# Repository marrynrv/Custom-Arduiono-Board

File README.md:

# Custom ATmega328PB Development Board 

A custom-designed development board built from scratch in **KiCad EDA**, based on the ATmega328PB microcontroller architecture and the classic Arduino Uno reference design. 

This project was created as a practical hands-on hardware engineering task to master schematic capture, SMD component placement, USB-to-UART interface integration, power regulation, and manufacturing output preparation.

---

## 3D Render & Hardware Preview

---

## Hardware Specifications & Key Features

* **Primary Microcontroller:** ATmega328PB-AU (TQFP-32 package)
* **USB-to-Serial Converter:** ATmega16U2-A with 16MHz Crystal Oscillator
* **Power Management:** 
  * NCP1117-5.0 LDO regulator for 5V main rail
  * LP2985-3.3 regulator for 3.3V power output
  * DC Barrel Jack & USB Micro (USB_B_Micro) input protection
* **ESD & Circuit Protection:** ESD protection array (CG00603MLC-05E) and resettable PTC fuse (MF-MSMF050-2)
* **Operational Amplifiers:** LMV358 for power source switching / indicator circuit
* **Programming Interfaces:** AVR-ISP-6 headers for direct flashing via ICSP
* **Design Tools:** KiCad EDA (Schematics, PCB Layout, Gerber generation, BOM export)

---

## Repository Content

* `arduino-board-pcb.kicad_sch` — Schematic source file
* `arduino-board-pcb.kicad_pcb` — PCB layout source file
* `arduino-board-pcb.kicad_pro` — KiCad main project file
* `arduino-board-pcb.csv` — Full Bill of Materials (BOM) with precise component specifications
* `pcb-arduino-gbr.rar` — Production-ready Gerber files
* `/images/board_3d.png` — 3D visualization render

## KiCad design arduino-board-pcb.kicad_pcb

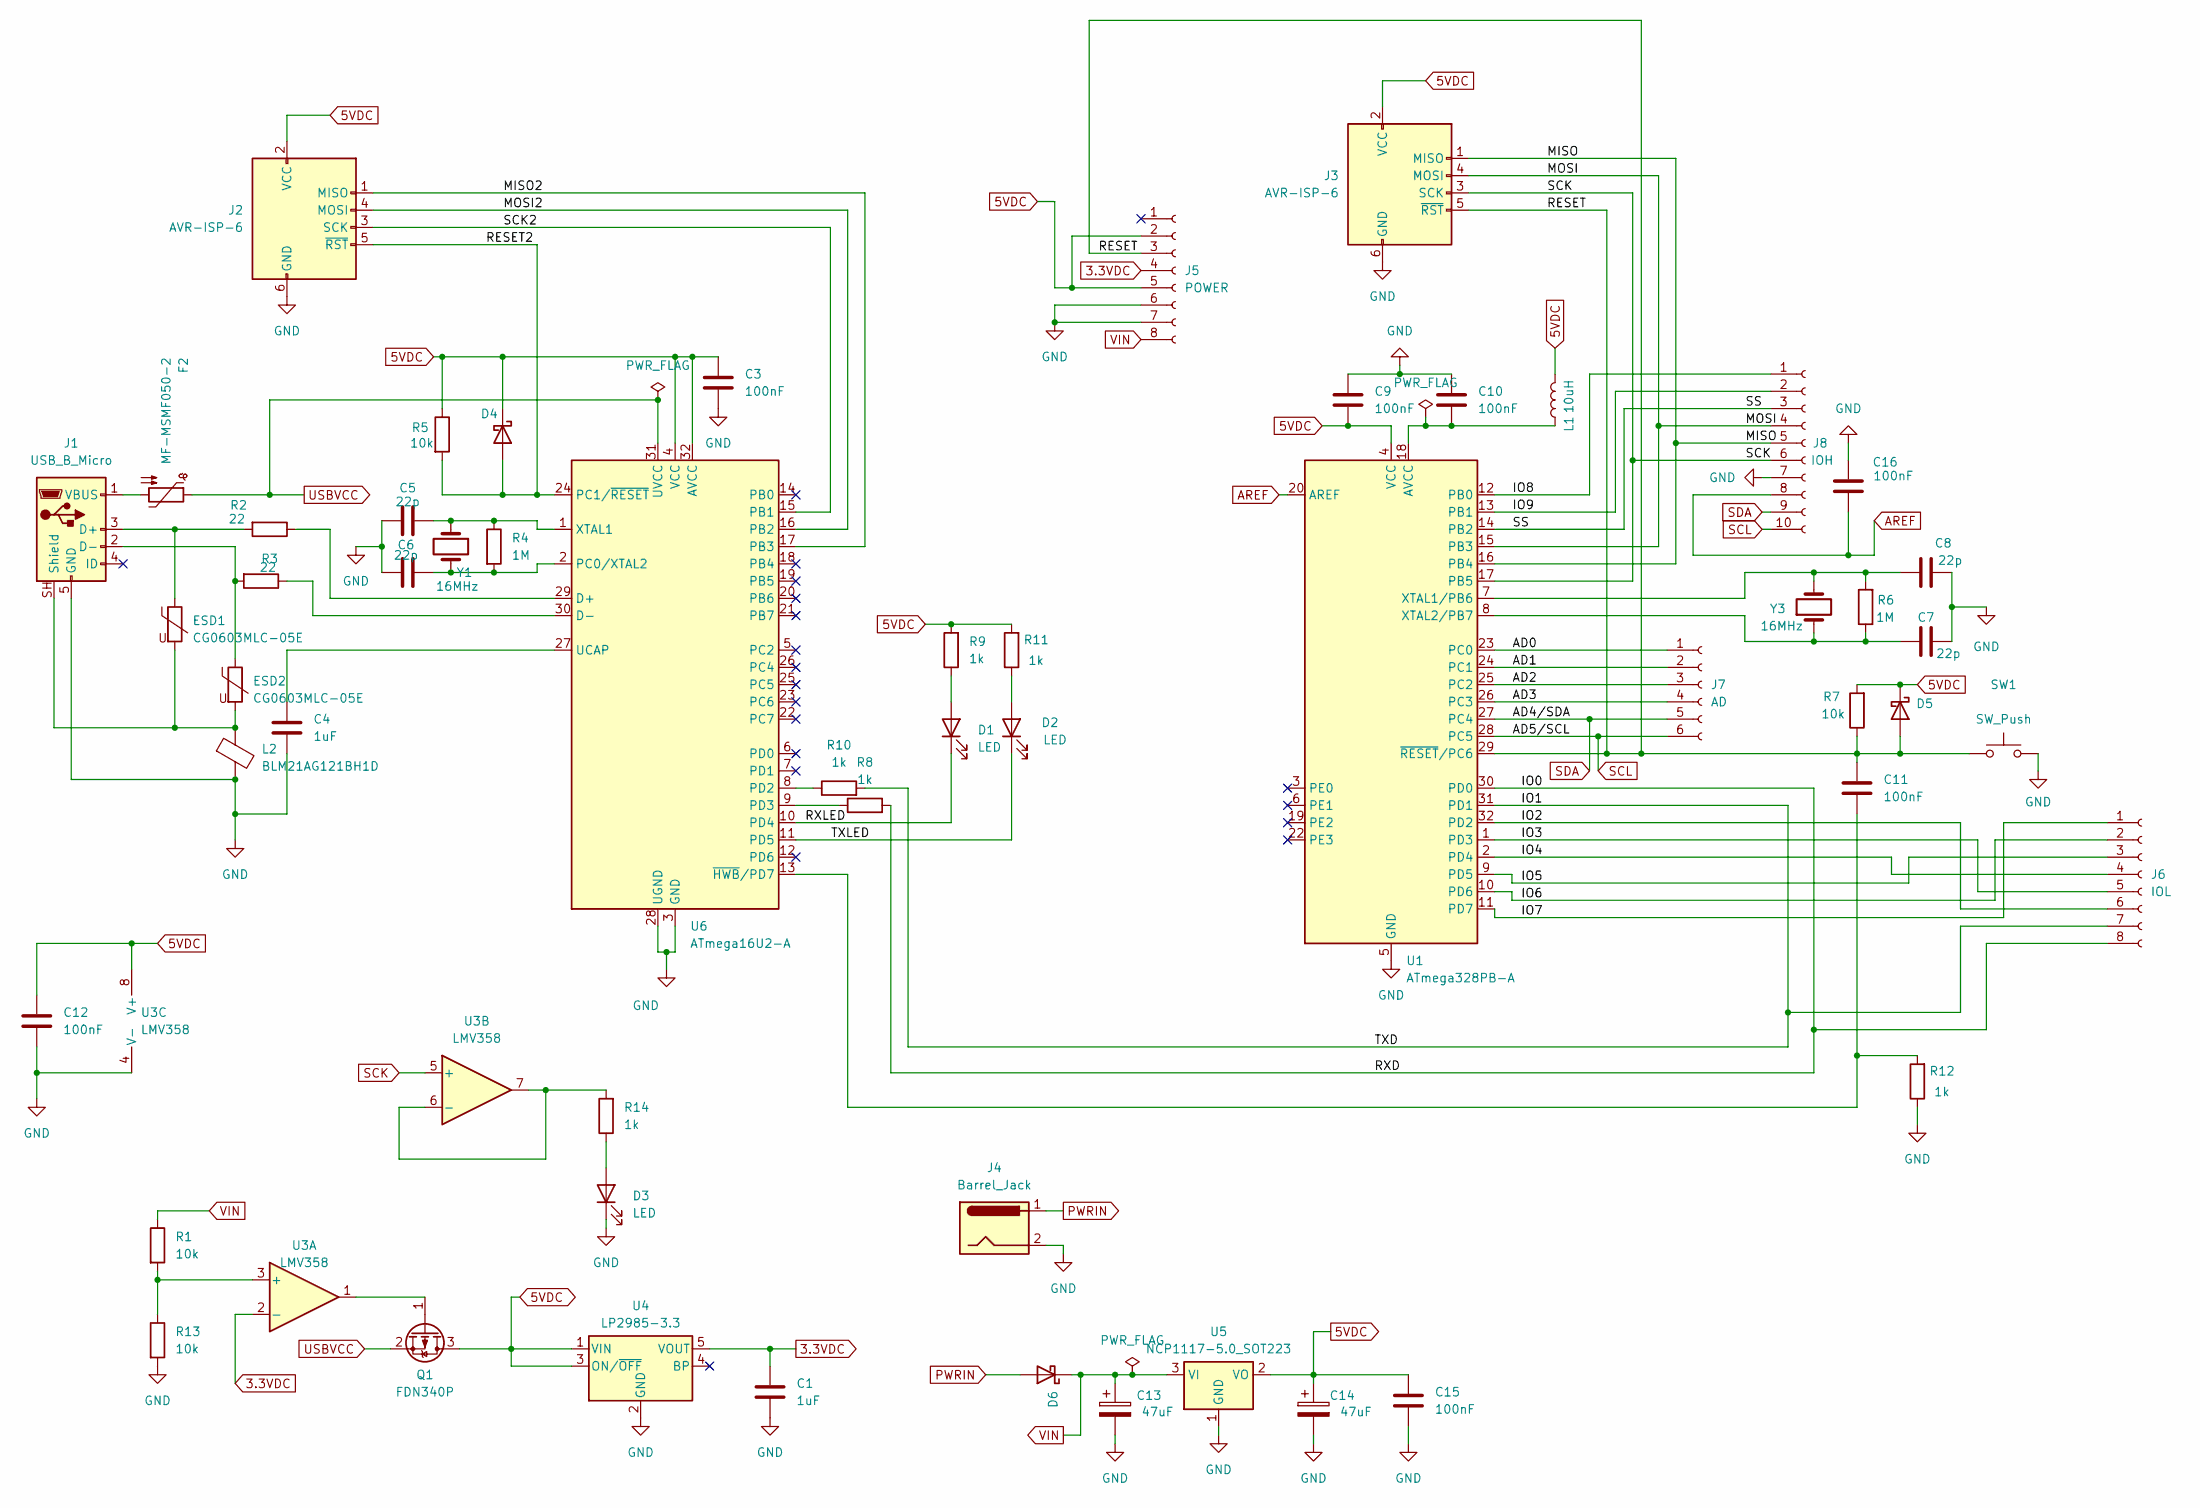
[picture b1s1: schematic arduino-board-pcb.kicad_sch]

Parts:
C1, C4: 1uF; C_0603_1608Metric
C3, C9, C10, C11, C12, C15, C16: 100nF; C_0603_1608Metric
C5, C6, C7, C8: 22p; C_0603_1608Metric
C13, C14: 47uF; CP_Elec_6.3x5.8
D1, D2, D3: LED; LED_0603_1608Metric
D4, D5, D6: CDBA340-HF; D_SMA
ESD1, ESD2: CG0603MLC-05E; R_0603_1608Metric
F2: MF-MSMF050-2; Fuse_1812_4532Metric
J1: USB_B_Micro; USB_Micro-B_Amphenol_10118193-0001LF_Horizontal
J2, J3: AVR-ISP-6; PinHeader_2x03_P2.54mm_Vertical_SMD
J4: Barrel_Jack; BarrelJack_SwitchcraftConxall_RAPC10U_Horizontal
J5: POWER; PinSocket_1x08_P2.54mm_Vertical
J6: IOL; PinSocket_1x08_P2.54mm_Vertical
J7: AD; PinSocket_1x06_P2.54mm_Vertical
J8: IOH; PinSocket_1x10_P2.54mm_Vertical
L1: 10uH; L_0603_1608Metric
L2: BLM21AG121BH1D; L_0805_2012Metric
Q1: FDN340P; SOT-23
R1, R5, R7, R13: 10k; R_0603_1608Metric
R2, R3: 22; R_0603_1608Metric
R4, R6: 1M; R_0603_1608Metric
R8, R9, R10, R11, R12, R14: 1k; R_0603_1608Metric
SW1: SW_Push; SW_Tactile_SPST_NO_Straight_CK_PTS636Sx25SMTRLFS
U1: ATmega328PB-A; TQFP-32_7x7mm_P0.8mm
U3: LMV358; MSOP-8_3x3mm_P0.65mm
U4: LP2985-3.3; SOT-23-5
U5: NCP1117-5.0_SOT223; SOT-223-3_TabPin2
U6: ATmega16U2-A; TQFP-32_7x7mm_P0.8mm
Y1, Y3: 16MHz; Crystal_SMD_Abracon_ABM3-2Pin_5.0x3.2mm

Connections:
3.3VDC: C1.1, J5.4, U3.2 (-), U4.5 (VOUT)
5VDC: C3.1, C9.2, C12.1, C14.1, C15.1, D4.1 (K), D5.1 (K), J2.2 (VCC), J3.2 (VCC), J5.2, J5.5, L1.2, Q1.3 (D), R5.1, R7.2, R9.2, R11.2, U1.4 (VCC), U3.8 (V+), U4.1 (VIN), U4.3 (ON/~OFF), U5.2 (VO), U6.4 (VCC), U6.32 (AVCC)
/AD0: J7.1, U1.23 (PC0)
/AD1: J7.2, U1.24 (PC1)
/AD2: J7.3, U1.25 (PC2)
/AD3: J7.4, U1.26 (PC3)
/IO0: J6.8, R8.2, U1.30 (PD0)
/IO1: J6.7, R10.2, U1.31 (PD1)
/IO2: J6.6, U1.32 (PD2)
/IO3: J6.5, U1.1 (PD3)
/IO4: J6.4, U1.2 (PD4)
/IO5: J6.3, U1.9 (PD5)
/IO6: J6.2, U1.10 (PD6)
/IO7: J6.1, U1.11 (PD7)
/IO8: J8.1, U1.12 (PB0)
/IO9: J8.2, U1.13 (PB1)
/MISO: J3.1 (MISO), J8.5, U1.16 (PB4)
/MISO2: J2.1 (MISO), U6.17 (PB3)
/MOSI: J3.4 (MOSI), J8.4, U1.15 (PB3)
/MOSI2: J2.4 (MOSI), U6.16 (PB2)
/RESET: C11.1, D5.2 (A), J3.5 (~RST), J5.3, R7.1, SW1.1, U1.29 (~RESET/PC6)
/RESET2: D4.2 (A), J2.5 (~RST), R5.2, U6.24 (PC1/~RESET)
/RXLED: D1.1 (K), U6.10 (PD4)
/SCK2: J2.3 (SCK), U6.15 (PB1)
/SS: J8.3, U1.14 (PB2)
/TXLED: D2.1 (K), U6.11 (PD5)
AREF: C16.1, J8.8, U1.20 (AREF)
GND: C1.2, C3.2, C4.2, C5.2, C6.2, C7.2, C8.2, C9.1, C10.1, C12.2, C13.2, C14.2, C15.2, C16.2, D3.1 (K), J1.5 (GND), J2.6 (GND), J3.6 (GND), J4.2, J5.6, J5.7, J8.7, L2.2, R12.1, R13.2, SW1.2, U1.5 (GND), U1.21 (GND), U3.4 (V-), U4.2 (GND), U5.1 (GND), U6.3 (GND), U6.28 (UGND)
unnamed: D1.2 (A), R9.1
unnamed: D2.2 (A), R11.1
unnamed: D3.2 (A), R14.1
unnamed: ESD1.1, J1.3 (D+), R2.2
unnamed: ESD2.1, J1.2 (D-), R3.2
unnamed: ESD1.2, ESD2.2, J1.SH (Shield), L2.1
unnamed: F2.2, J1.1 (VBUS)
unnamed: Q1.1 (G), U3.1
unnamed: C10.2, L1.1, U1.18 (AVCC)
unnamed: C8.1, R6.2, U1.7 (XTAL1/PB6), Y3.2
unnamed: C7.1, R6.1, U1.8 (XTAL2/PB7), Y3.1
unnamed: R1.2, R13.1, U3.3 (+)
unnamed: R14.2, U3.6 (-), U3.7
unnamed: R2.1, U6.29 (D+)
unnamed: R3.1, U6.30 (D-)
unnamed: C6.1, R4.2, U6.2 (PC0/XTAL2), Y1.2
unnamed: R10.1, U6.8 (PD2)
unnamed: R8.1, U6.9 (PD3)
unnamed: C4.1, U6.27 (UCAP)
unnamed: C5.1, R4.1, U6.1 (XTAL1), Y1.1
unnamed: C11.2, R12.2, U6.13 (~HWB/PD7)
PWRIN: D6.2 (A), J4.1
SCK: J3.3 (SCK), J8.6, U1.17 (PB5), U3.5 (+)
SCL: J7.6, J8.10, U1.28 (PC5)
SDA: J7.5, J8.9, U1.27 (PC4)
USBVCC: F2.1, Q1.2 (S), U6.31 (UVCC)
VIN: C13.1, D6.1 (K), J5.8, R1.1, U5.3 (VI)

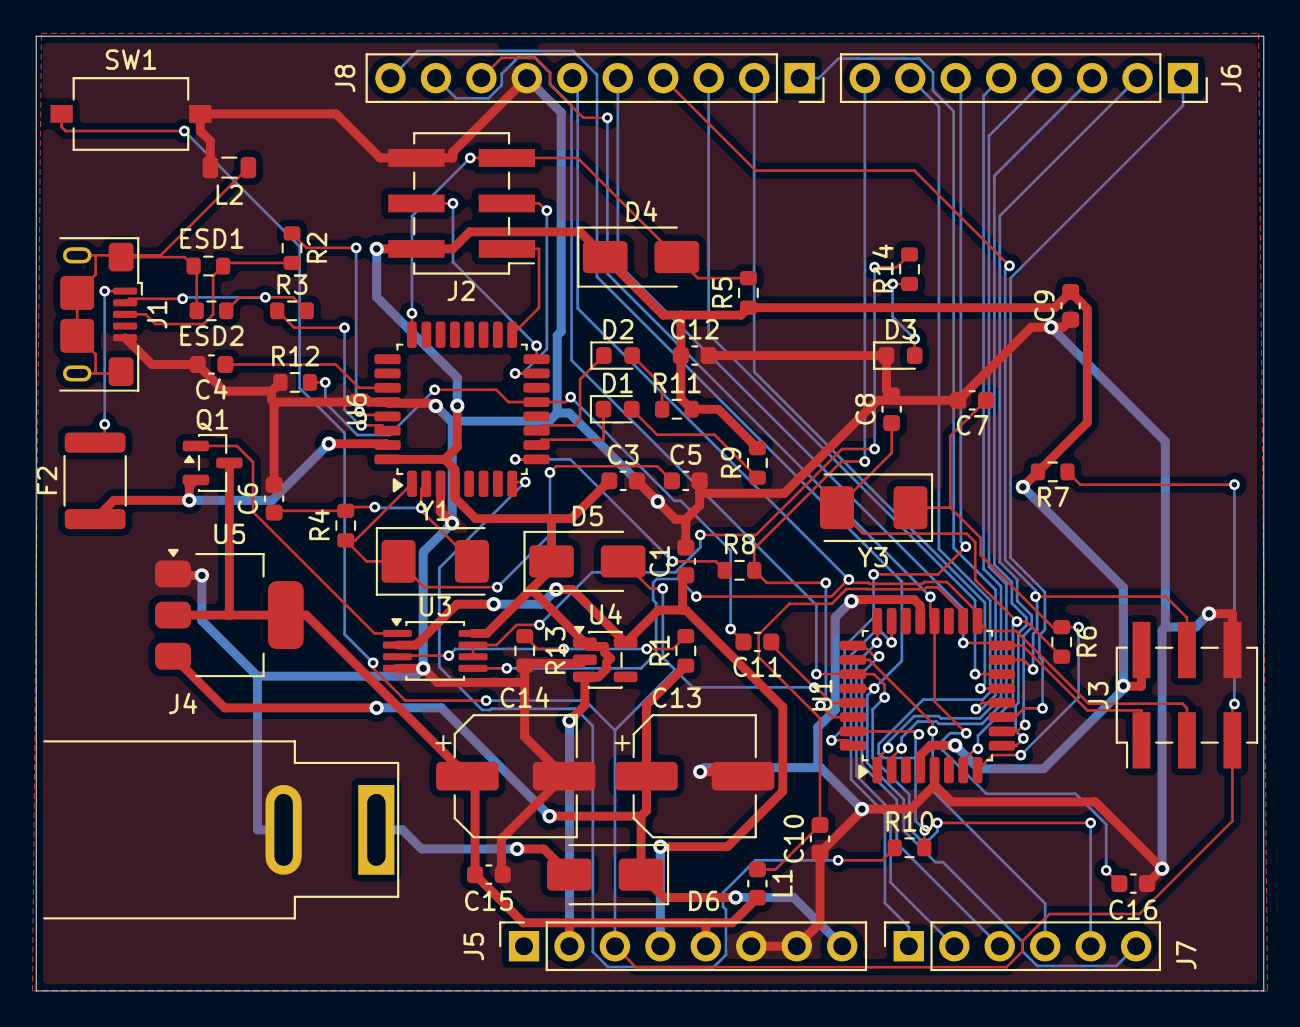
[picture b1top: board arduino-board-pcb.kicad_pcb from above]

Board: 2 copper layers, 68.6 x 53.3 mm, 57 parts (0 on the bottom side), 55 nets.
